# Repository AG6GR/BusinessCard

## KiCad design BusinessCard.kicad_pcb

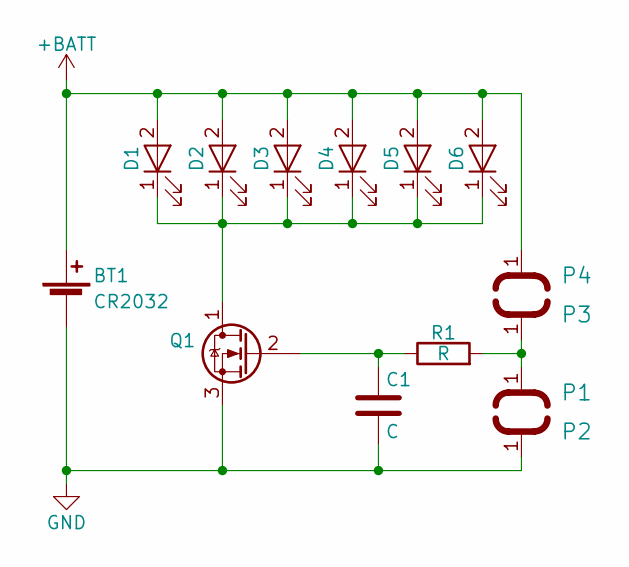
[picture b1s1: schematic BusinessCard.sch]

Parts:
BT1: CR2032; Linx_CR2032_Holder
C1: C; C_1206_HandSoldering
D1, D2, D3, D4, D5, D6: LED; LED_1206
P1, P2, P3, P4: ButtonPad
Q1: Q_NMOS_DGS; SOT-23_Handsoldering
R1: R; R_1206_HandSoldering

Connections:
+3V3: BT1.1 (+), D1.2 (A), D2.2 (A), D3.2 (A), D4.2 (A), D5.2 (A), D6.2 (A), P4.1
Cathode: D1.1 (K), D2.1 (K), D3.1 (K), D4.1 (K), D5.1 (K), D6.1 (K), Q1.1 (D)
GND: BT1.2 (-), C1.2, P2.1, Q1.3 (S)
unnamed: C1.1, Q1.2 (G), R1.1
Sense: P1.1, P3.1, R1.2

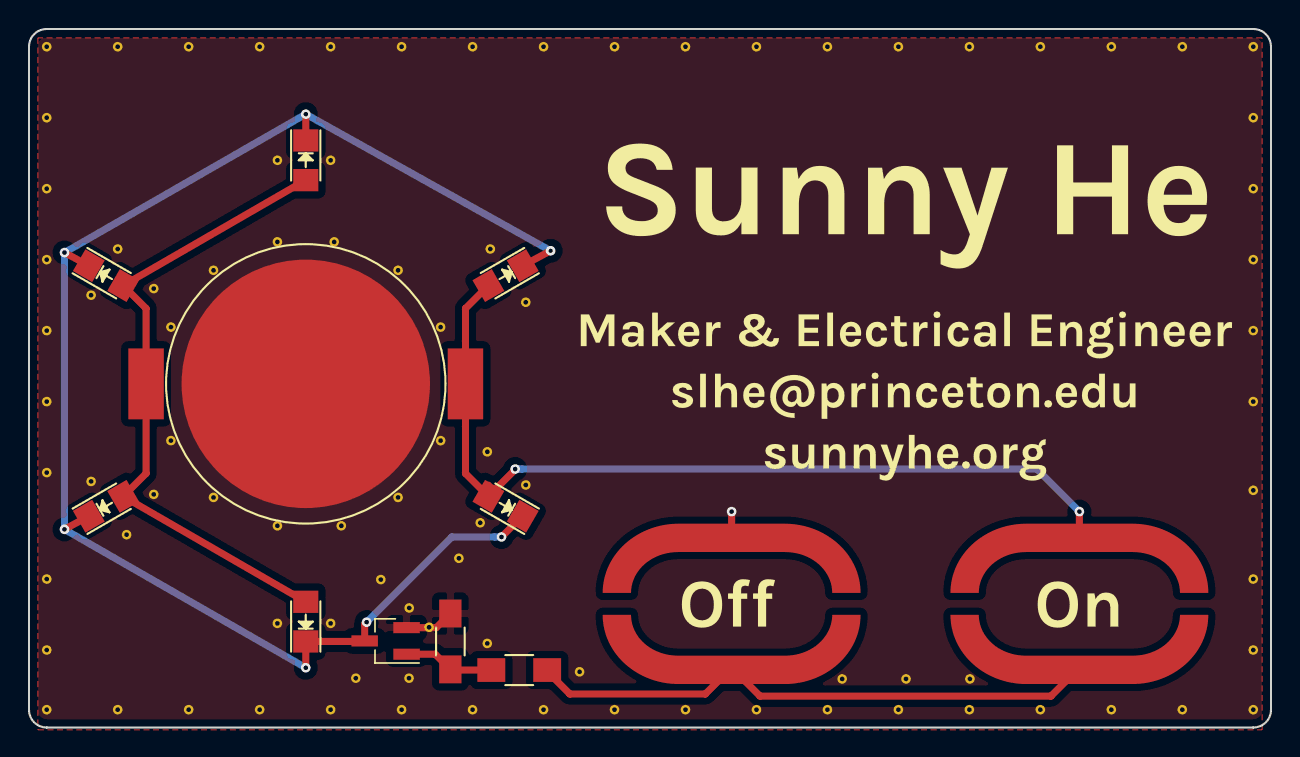
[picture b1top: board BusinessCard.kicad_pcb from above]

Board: 2 copper layers, 88.9 x 50.0 mm, 15 parts (0 on the bottom side), 5 nets.

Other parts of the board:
svg2mod: G***; front

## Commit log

2017-09-24 First draft of front
2017-09-25 Front placement complete
2017-09-25 Preliminary routing
2017-09-25 Finish stitching, fixed pad assignments
2017-09-25 Adjust board size
2017-09-29 Add filtering components, back silkscreen
2017-09-29 Exported gerbers for order rev1
2017-09-29 Add schematic output
2017-10-16 Create LICENSE
2017-10-16 Restore svg layout
